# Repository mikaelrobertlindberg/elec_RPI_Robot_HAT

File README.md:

# Robot HAT D1-M1 — PCBWay prototype package

**Current fork revision: D1-M1, ten assembled prototype boards.** Use [the complete M1 PCBA archive](production/M1/Robot_HAT_M1_PCBA_10.zip), [ordering instructions](ORDERING.md) and [qualification record](QUALIFICATION.md). Original D1 production files below are historical. M1 targets a 2S battery (6.0–8.4 V) and a combined 5 V load up to 2 A; the original 5–28 V statement is superseded for this revision.

M1 corrects U12 pad/mask spacing, audio filter labels, component sourcing/pinouts and the regulator/ideal-diode circuit. It includes coherent Gerber, drills, BOM, placement, assembly drawings and dated sourcing. Native checks and export verification are recorded in the package. Physical prototype testing remains required.

## Original upstream description

> "RPI_Robot_HAT" is a raspberry pi HAT designed for small/medium size robots. It has an IMU, Dynamixel connectors and audio. Its size fits a Raspberry PI zero.

The RPI_Robot_HAT gathers:

- **IMU** over I2C + data fusion
- **Dynamixel motor communication**: both TTL and 485 to drive Dynamixel/Feetech motor (requires cable adaptation)
- **in/out audio device** with an integrated mems microphone. Wago connectors allows connection of loudspeaker and extra microphone.
- **expension Qwiic connectors**, 1 mm/3V3. Please refer to the schematic for knowing which can be use on you raspberry pi.

The RPI_Robot_HAT can be power from 5 to 28V. It is designed to use of the motor connector as an power input.

## Releases
| Release | Date       | Designer | Check  | Comments                               |
|---------|------------|----------|--------|----------------------------------------|
| A1      | 06/03/2026 | EB       | SN     | Initial drawing                        |
| B1      | 06/05/2026 | EB       | SN     |[fixed] Acc. is at 0x19 I2C address<br />[fixed] Soft reset of the audio DAC<br />[fixed] Ideal diode<br />[fixed] Know position of IMU<br />[update] Dynamixel_dir is based on Tx<br />[added] IMU can be disconnected<br />[added] IMU_IT is cabled<br />[added] Access to I2C0<br />[added] Switch off detection|
| C1      | 08/07/2026 | EB       | SN     | [fix] 3V3 on IO10/11<br />[fix] MOS direction of Ideal diode<br />[update] I2C3 is by default instead of reserved I2C|
| D1      | 06/10/2026 | EB       | Claude | [update] IMU is now LSM6DSV16XTR<br />[update] RS485 Driver<br /> [update] screwable terminals for audio|

## Basically
 - Designed with KiCAD 9.

## Rebuilding M1

The checked-in production/M1 archive is ready for supplier review. To reproduce it, use KiCad9 CLI/Python and Python3 with shapely, gerbonara and PyMuPDF, then run python build_release.py. The builder runs physical connectivity, the deliberate U12 negative control, native all-severity checks and export reconciliation before packaging. --package-only refreshes packaging from existing exports and requires an up-to-date native connectivity report; it does not export new CAD data.

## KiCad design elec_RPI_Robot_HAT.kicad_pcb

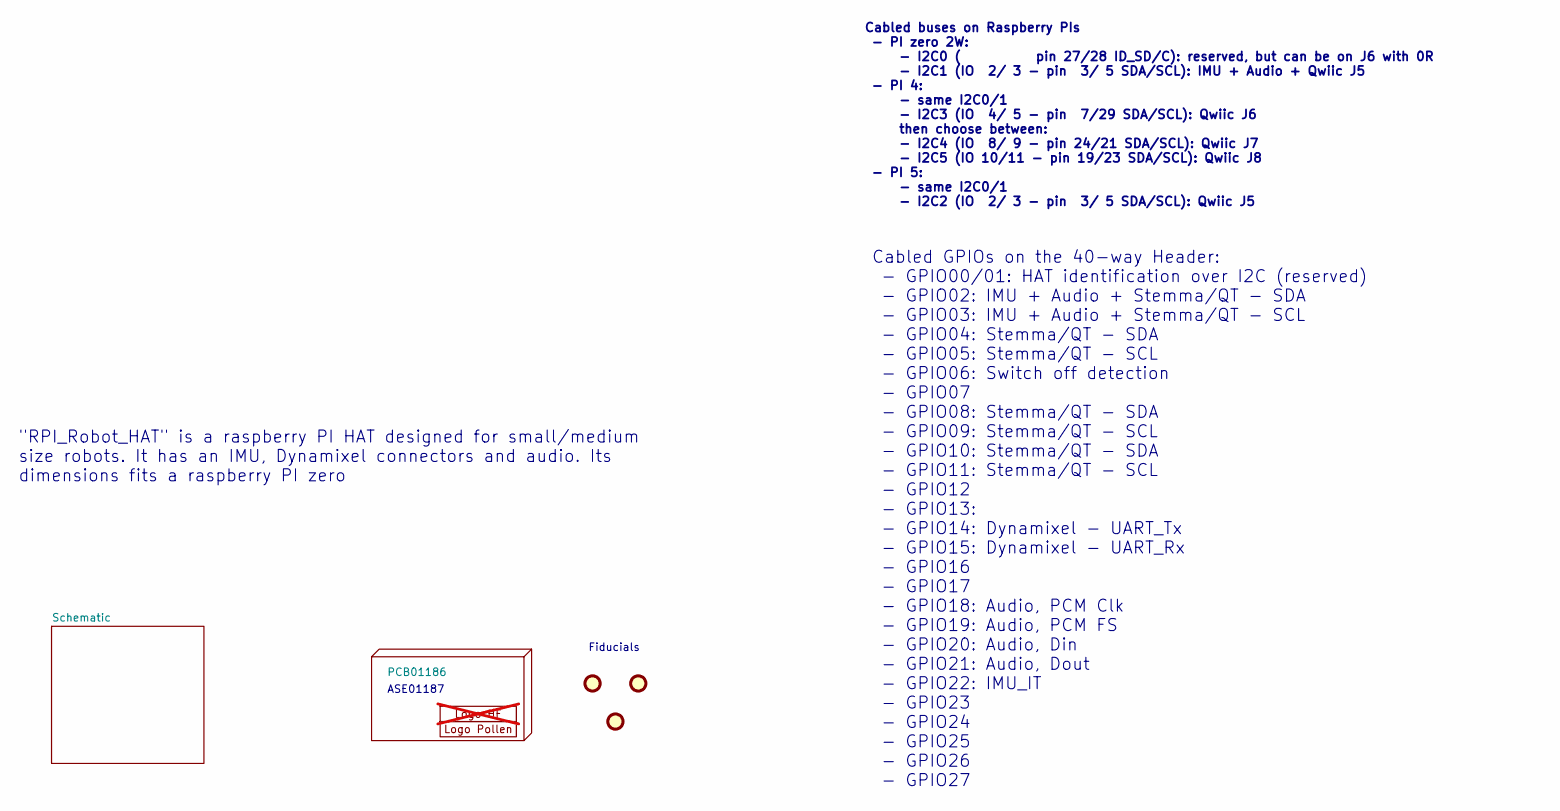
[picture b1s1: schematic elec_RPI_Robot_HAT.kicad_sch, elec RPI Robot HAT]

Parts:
FID1: DNP Fiducial; Fiducial_1mm_Mask2mm_FID1
FID2: DNP Fiducial; Fiducial_1mm_Mask2mm_FID2
FID3: DNP Fiducial; Fiducial_1mm_Mask2mm_FID3
H1: PCB01186
H2: Logo HF 2025; Logo_HF_2025_H2; not fitted
H3: DNP Logo Pollen 2021; Logo_Pollen_2021_sq_H3

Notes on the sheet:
Fiducials
Cabled buses on Raspberry PIs - PI zero 2W: - I2C0 ( pin 27/28 ID_SD/C): reserved, but can be on J6 with 0R - I2C1 (IO 2/ 3 - pin 3/ 5 SDA/SCL): IMU + Audio + Qwiic J5 - PI 4: - same I2C0/1 - I2C3 (IO 4/ 5 - pin 7/29 SDA/SCL): Qwiic J6 then choose between: - I2C4 (IO 8/ 9 - pin 24/21 SDA/SCL): Qwii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
ASE01187
"RPI_Robot_HAT" is a raspberry PI HAT designed for small/medium size robots. It has an IMU, Dynamixel connectors and audio. Its dimensions fits a raspberry PI zero
Cabled GPIOs on the 40-way Header: - GPIO00/01: HAT identification over I2C (reserved) - GPIO02: IMU + Audio + Stemma/QT - SDA - GPIO03: IMU + Audio + Stemma/QT - SCL - GPIO04: Stemma/QT - SDA - GPIO05: Stemma/QT - SCL - GPIO06: Switch off detection - GPIO07 - GPIO08: Stemma/QT - SDA - GPIO09: Stem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

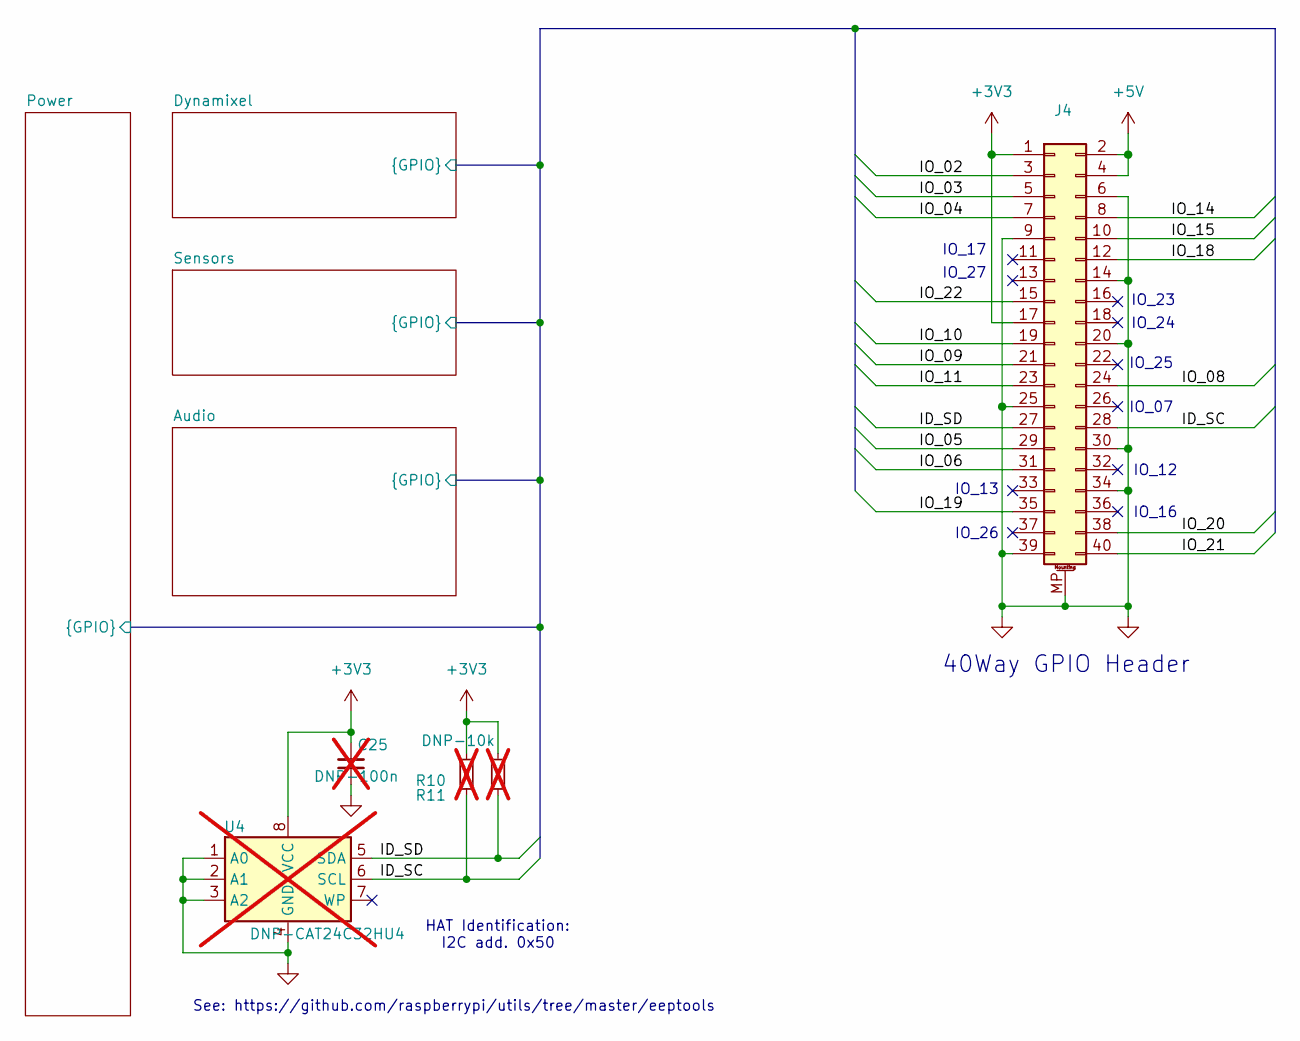
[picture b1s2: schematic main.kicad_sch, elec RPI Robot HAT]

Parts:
C25: DNP-100n; C_0402_1005Metric_C25; not fitted
J4: Female Header 2x20 SMD; PinHeader_2x20_P2.54mm_Vertical_with_rasp_HAT_zero_SMD_conn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; Part Description PinHeader_2x20_P2.54mm_Vertical; LCSC Part C2685112
R10: DNP-10k; R_0402_1005Metric_R10; not fitted
R11: DNP-10k; R_0402_1005Metric_R11; not fitted
U4: DNP-CAT24C32HU4; TDFN-8_L3.0-W2.0-P0.50-BL-EP_U4; not fitted

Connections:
+3V3: C25.2, J4.1, J4.17, R10.1, R11.1, U4.8 (VCC); also elsewhere on the board
+5V: J4.2, J4.4; also elsewhere on the board
/Schematic/Audio/ID_SC: J4.28, R10.2, U4.6 (SCL); also elsewhere on the board
/Schematic/Audio/ID_SD: J4.27, R11.2, U4.5 (SDA); also elsewhere on the board
/Schematic/Audio/IO_02: J4.3; also elsewhere on the board
/Schematic/Audio/IO_03: J4.5; also elsewhere on the board
/Schematic/Audio/IO_04: J4.7; also elsewhere on the board
/Schematic/Audio/IO_05: J4.29; also elsewhere on the board
/Schematic/Audio/IO_06: J4.31; also elsewhere on the board
/Schematic/Audio/IO_08: J4.24; also elsewhere on the board
/Schematic/Audio/IO_09: J4.21; also elsewhere on the board
/Schematic/Audio/IO_10: J4.19; also elsewhere on the board
/Schematic/Audio/IO_11: J4.23; also elsewhere on the board
/Schematic/Audio/IO_14: J4.8; also elsewhere on the board
/Schematic/Audio/IO_15: J4.10; also elsewhere on the board
/Schematic/Audio/IO_18: J4.12; also elsewhere on the board
/Schematic/Audio/IO_19: J4.35; also elsewhere on the board
/Schematic/Audio/IO_20: J4.38; also elsewhere on the board
/Schematic/Audio/IO_21: J4.40; also elsewhere on the board
/Schematic/Audio/IO_22: J4.15; also elsewhere on the board
GND: C25.1, J4.6, J4.9, J4.14, J4.20, J4.25, J4.30, J4.34, J4.39, J4.MP (MountPin), U4.1 (A0), U4.2 (A1), U4.3 (A2), U4.4 (GND); also elsewhere on the board

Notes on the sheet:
IO_07
IO_23
40Way GPIO Header
IO_13
IO_24
HAT Identification: I2C add. 0x50
IO_25
IO_17
IO_12
See: https://github.com/raspberrypi/utils/tree/master/eeptools
IO_16
IO_26
IO_27

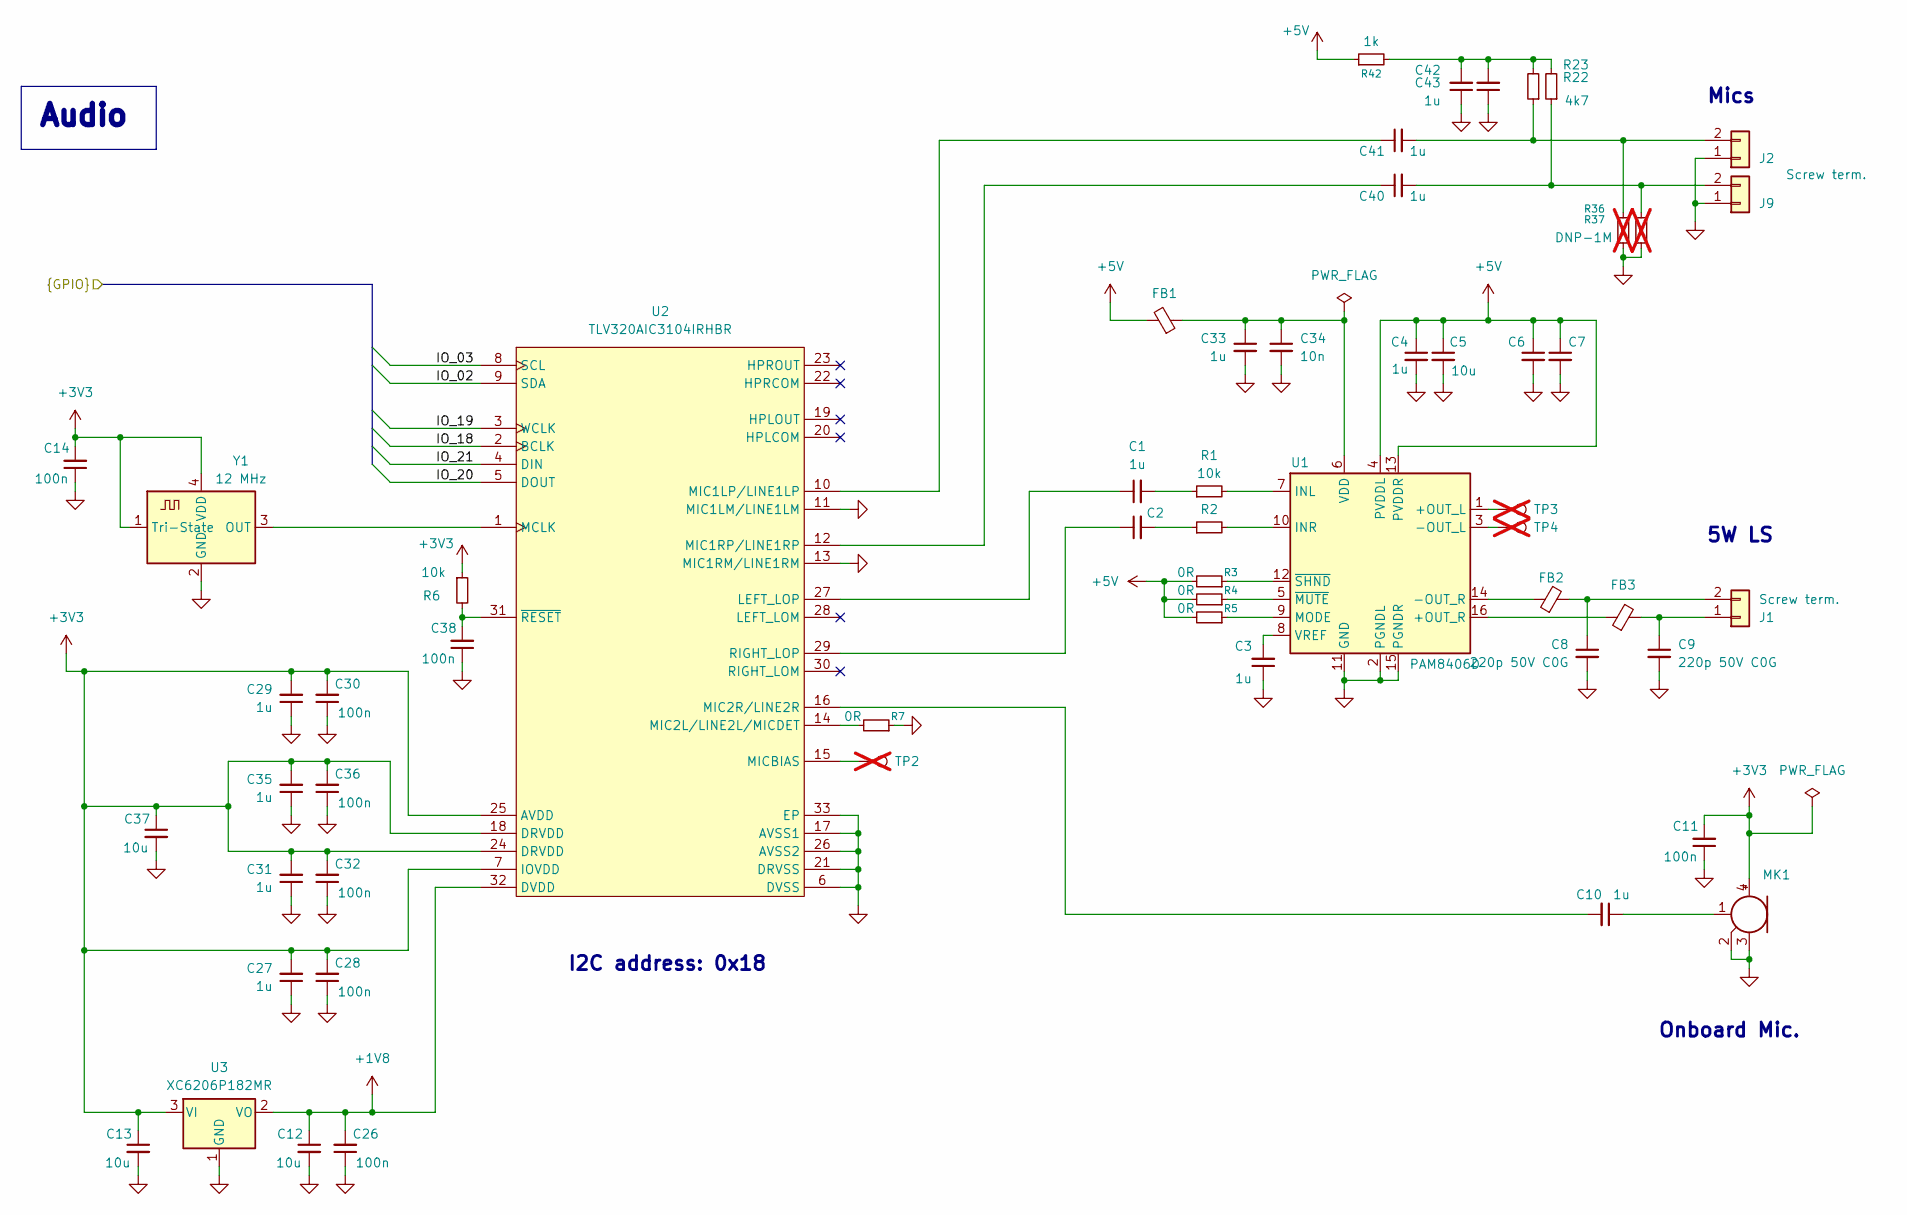
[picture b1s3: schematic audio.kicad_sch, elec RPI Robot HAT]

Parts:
C1: 1u; C_0402_1005Metric_C1; LCSC Part C52923
C2: 1u; C_0402_1005Metric_C2; LCSC Part C52923
C3: 1u; C_0402_1005Metric_C3; LCSC Part C52923
C4: 1u; C_0402_1005Metric_C4; LCSC Part C52923
C5: 10u; C_0603_1608Metric_C5; LCSC Part C1691
C6: 1u; C_0402_1005Metric_C6; LCSC Part C52923
C7: 10u; C_0603_1608Metric_C7; LCSC Part C1691
C8: 220p 50V C0G; C_0402_1005Metric_C8; LCSC Part C71693
C9: 220p 50V C0G; C_0402_1005Metric_C9; LCSC Part C71693
C10: 1u; C_0402_1005Metric_C10; LCSC Part C52923
C11: 100n; C_0402_1005Metric_C11; LCSC Part C307331
C12: 10u; C_0603_1608Metric_C12; LCSC Part C1691
C13: 10u; C_0603_1608Metric_C13; LCSC Part C1691
C14: 100n; C_0402_1005Metric_C14; LCSC Part C307331
C26: 100n; C_0402_1005Metric_C26; LCSC Part C307331
C27: 1u; C_0402_1005Metric_C27; LCSC Part C52923
C28: 100n; C_0402_1005Metric_C28; LCSC Part C307331
C29: 1u; C_0402_1005Metric_C29; LCSC Part C52923
C30: 100n; C_0402_1005Metric_C30; LCSC Part C307331
C31: 1u; C_0402_1005Metric_C31; LCSC Part C52923
C32: 100n; C_0402_1005Metric_C32; LCSC Part C307331
C33: 1u; C_0402_1005Metric_C33; LCSC Part C52923
C34: 10n; C_0402_1005Metric_C34; LCSC Part C15195
C35: 1u; C_0402_1005Metric_C35; LCSC Part C52923
C36: 100n; C_0402_1005Metric_C36; LCSC Part C307331
C37: 10u; C_0603_1608Metric_C37; LCSC Part C1691
C38: 100n; C_0402_1005Metric_C38; LCSC Part C307331
C40: 1u; C_0402_1005Metric_C40; LCSC Part C52923
C41: 1u; C_0402_1005Metric_C41; LCSC Part C52923
C42: 1u; C_0402_1005Metric_C42; LCSC Part C52923
C43: 1u; C_0402_1005Metric_C43; LCSC Part C52923
FB1: 0.3A 600R@100MHz; L_0402_1005Metric_FB1; LCSC Part C76884
FB2: 2A - 120R@100MHz; L_0402_1005Metric_FB2; LCSC Part C88970
FB3: 2A - 120R@100MHz; L_0402_1005Metric_FB3; LCSC Part C88970
J1: Screw term.; CONN-TH_DB125-2.54-2P-GN_J1; LCSC Part C918120
J2: Screw term.; CONN-TH_DB125-2.54-2P-GN_J2; LCSC Part C918120
J9: Screw term.; CONN-TH_DB125-2.54-2P-GN_J9; LCSC Part C918120
MK1: Microphone_MEMS; MIC-SMD_4P-L2.8-W1.9-P1.84-TL_MK1; LCSC Part C7587901
R1: 10k; R_0402_1005Metric_R1; LCSC Part C25744
R2: 10k; R_0402_1005Metric_R2; LCSC Part C25744
R3: 0R; R_0402_1005Metric_R3; LCSC Part C17168
R4: 0R; R_0402_1005Metric_R4; LCSC Part C17168
R5: 0R; R_0402_1005Metric_R5; LCSC Part C17168
R6: 10k; R_0402_1005Metric_R6; LCSC Part C25744
R7: 0R; R_0402_1005Metric_R7; LCSC Part C17168
R22: 4k7; R_0402_1005Metric_R22; LCSC Part C105871
R23: 4k7; R_0402_1005Metric_R23; LCSC Part C105871
R36: DNP-1M; R_0402_1005Metric_R36; not fitted
R37: DNP-1M; R_0402_1005Metric_R37; not fitted
R42: 1k; R_0402_1005Metric_R42; LCSC Part C105637
TP2: TestPoint; TestPoint_Loop_D2.50mm_Drill1.0mm_LowProfile_TP2; not fitted
TP3: TestPoint; TestPoint_Loop_D2.50mm_Drill1.0mm_LowProfile_TP3; not fitted
TP4: TestPoint; TestPoint_Loop_D2.50mm_Drill1.0mm_LowProfile_TP4; not fitted
U1: PAM8406D; SOIC-16_3.9x9.9mm_P1.27mm_U1; LCSC Part C86270
U2: TLV320AIC3104IRHBR; VQFN-32-1EP_5x5mm_P0.5mm_EP3.5x3.5mm_U2; LCSC Part C181753
U3: XC6206P182MR; SOT-23-3_U3; LCSC Part C347373
Y1: 12 MHz; Oscillator_SMD_Abracon_ASDMB-4Pin_2.5x2.0mm_Y1; LCSC Part C7425459

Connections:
+1V8: C12.1, C26.2, U2.32 (DVDD), U3.2 (VO)
+3V3: C11.2, C13.1, C14.2, C27.2, C28.2, C29.2, C30.2, C31.2, C32.2, C35.2, C36.2, C37.1, MK1.4 (+), R6.1, U2.7 (IOVDD), U2.18 (DRVDD), U2.24 (DRVDD), U2.25 (AVDD), U3.3 (VI), Y1.1 (Tri-State), Y1.4 (VDD); also elsewhere on the board
+5V: C4.1, C5.1, C6.1, C7.1, FB1.2, R3.2, R4.2, R5.2, R42.1, U1.4 (PVDDL), U1.13 (PVDDR); also elsewhere on the board
/Schematic/Audio/IO_02: U2.9 (SDA); also elsewhere on the board
/Schematic/Audio/IO_03: U2.8 (SCL); also elsewhere on the board
/Schematic/Audio/IO_18: U2.2 (BCLK); also elsewhere on the board
/Schematic/Audio/IO_19: U2.3 (WCLK); also elsewhere on the board
/Schematic/Audio/IO_20: U2.5 (DOUT); also elsewhere on the board
/Schematic/Audio/IO_21: U2.4 (DIN); also elsewhere on the board
GND: C3.1, C4.2, C5.2, C6.2, C7.2, C8.2, C9.2, C11.1, C12.2, C13.2, C14.1, C26.1, C27.1, C28.1, C29.1, C30.1, C31.1, C32.1, C33.2, C34.2, C35.1, C36.1, C37.2, C38.1, C42.1, C43.1, J2.1, J9.1, MK1.2 (-), MK1.3 (-), R7.1, R36.1, R37.1, U1.2 (PGNDL), U1.11 (GND), U1.15 (PGNDR), U2.6 (DVSS), U2.11 (MIC1LM/LINE1LM), U2.13 (MIC1RM/LINE1RM), U2.17 (AVSS1), U2.21 (DRVSS), U2.26 (AVSS2), U2.33 (EP), U3.1 (GND), Y1.2 (GND); also elsewhere on the board
unnamed: C1.2, R1.1
unnamed: C2.2, R2.1
unnamed: C10.1, MK1.1 (-)
unnamed: C42.2, C43.2, R22.2, R23.2, R42.2
unnamed: C9.1, FB3.2, J1.1
unnamed: C8.1, FB2.2, J1.2
unnamed: C41.2, J2.2, R22.1, R36.2
unnamed: C40.2, J9.2, R23.1, R37.2
unnamed: TP3.1, U1.1 (+OUT_L)
unnamed: FB3.1, U1.16 (+OUT_R)
unnamed: TP4.1, U1.3 (-OUT_L)
unnamed: FB2.1, U1.14 (-OUT_R)
unnamed: R1.2, U1.7 (INL)
unnamed: R2.2, U1.10 (INR)
unnamed: R5.1, U1.9 (MODE)
unnamed: C33.1, C34.1, FB1.1, U1.6 (VDD)
unnamed: C3.2, U1.8 (VREF)
unnamed: R4.1, U1.5 (~MUTE)
unnamed: R3.1, U1.12 (~SHND)
unnamed: C1.1, U2.27 (LEFT_LOP)
unnamed: U2.1 (MCLK), Y1.3 (OUT)
unnamed: C41.1, U2.10 (MIC1LP/LINE1LP)
unnamed: C40.1, U2.12 (MIC1RP/LINE1RP)
unnamed: R7.2, U2.14 (MIC2L/LINE2L/MICDET)
unnamed: C10.2, U2.16 (MIC2R/LINE2R)
unnamed: TP2.1, U2.15 (MICBIAS)
unnamed: C2.1, U2.29 (RIGHT_LOP)
unnamed: C38.2, R6.2, U2.31 (~RESET)

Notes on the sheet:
Onboard Mic.
5W LS
Mics
I2C address: 0x18
Audio

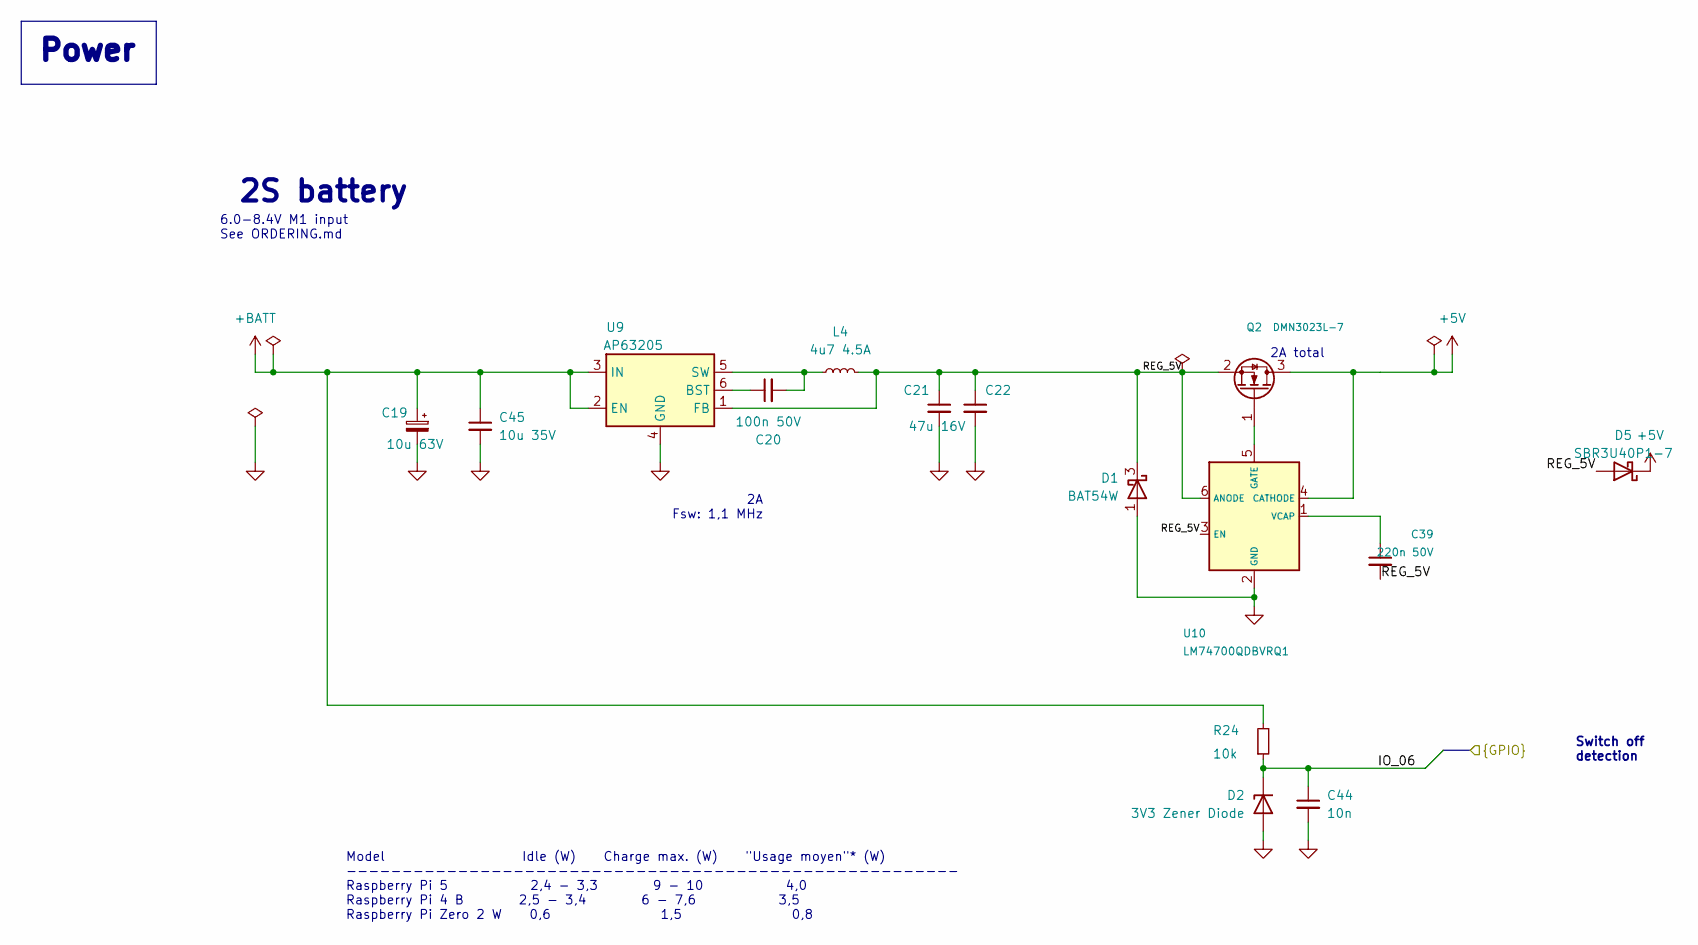
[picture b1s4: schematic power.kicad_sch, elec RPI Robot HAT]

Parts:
C19: 10u 63V; Panasonic_FK_D_6.3x5.8_C19
C20: 100n 50V; C_0402_1005Metric_C20; LCSC Part C307331
C21: 47u 16V; C_1206_C21; LCSC Part C385047
C22: 47u 16V; C_1206_C22; LCSC Part C385047
C39: 220n 50V; C_0805_C39; LCSC Part C86042
C44: 10n; C_0402_1005Metric_C44; LCSC Part C15195
C45: 10u 35V; C_0805_2012Metric_C45; LCSC Part C33546007
D1: BAT54W; SOT-323_SC-70_D1
D2: 3V3 Zener Diode; D_SOD-123_D2; LCSC Part C19077392
D5: SBR3U40P1-7; D_PowerDI123_D5; LCSC Part C97127
L4: 4u7 4.5A; Eaton_SDCHA1V6045_L4
Q2: DMN3023L-7; TSOT-23_Q2; LCSC Part C443825
R24: 10k; R_0402_1005Metric_R24; LCSC Part C25744
U9: AP63205; TSOT-23-6_U9; LCSC Part C2071056
U10: LM74700QDBVRQ1; LM74700_DBV_U10; LCSC Part C2941042

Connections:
+5V: D5.1 (K), Q2.3 (D), U10.4 (CATHODE); also elsewhere on the board
+BATT: C19.1, C45.1, R24.2, U9.2 (EN), U9.3 (IN); also elsewhere on the board
/Schematic/Audio/IO_06: C44.1, D2.1 (K), R24.1; also elsewhere on the board
/Schematic/Power/REG_5V: C21.1, C22.1, C39.2, D1.3 (K), D5.2 (A), L4.1, Q2.2 (S), U9.1 (FB), U10.3 (EN), U10.6 (ANODE)
GND: C19.2, C21.2, C22.2, C44.2, C45.2, D1.1 (A), D2.2 (A), U9.4 (GND), U10.2 (GND); also elsewhere on the board
unnamed: Q2.1 (G), U10.5 (GATE)
unnamed: C20.1, U9.6 (BST)
unnamed: C20.2, L4.2, U9.5 (SW)
unnamed: C39.1, U10.1 (VCAP)

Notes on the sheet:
Switch off detection
2A total
2S battery
Model Idle (W) Charge max. (W) "Usage moyen"* (W) ------------------------------------------------------- Raspberry Pi 5 2,4 - 3,3 9 - 10 4,0 Raspberry Pi 4 B 2,5 - 3,4 6 - 7,6 3,5 Raspberry Pi Zero 2 W 0,6 1,5 0,8
6.0-8.4V M1 input See ORDERING.md
2A Fsw: 1,1 MHz
Power

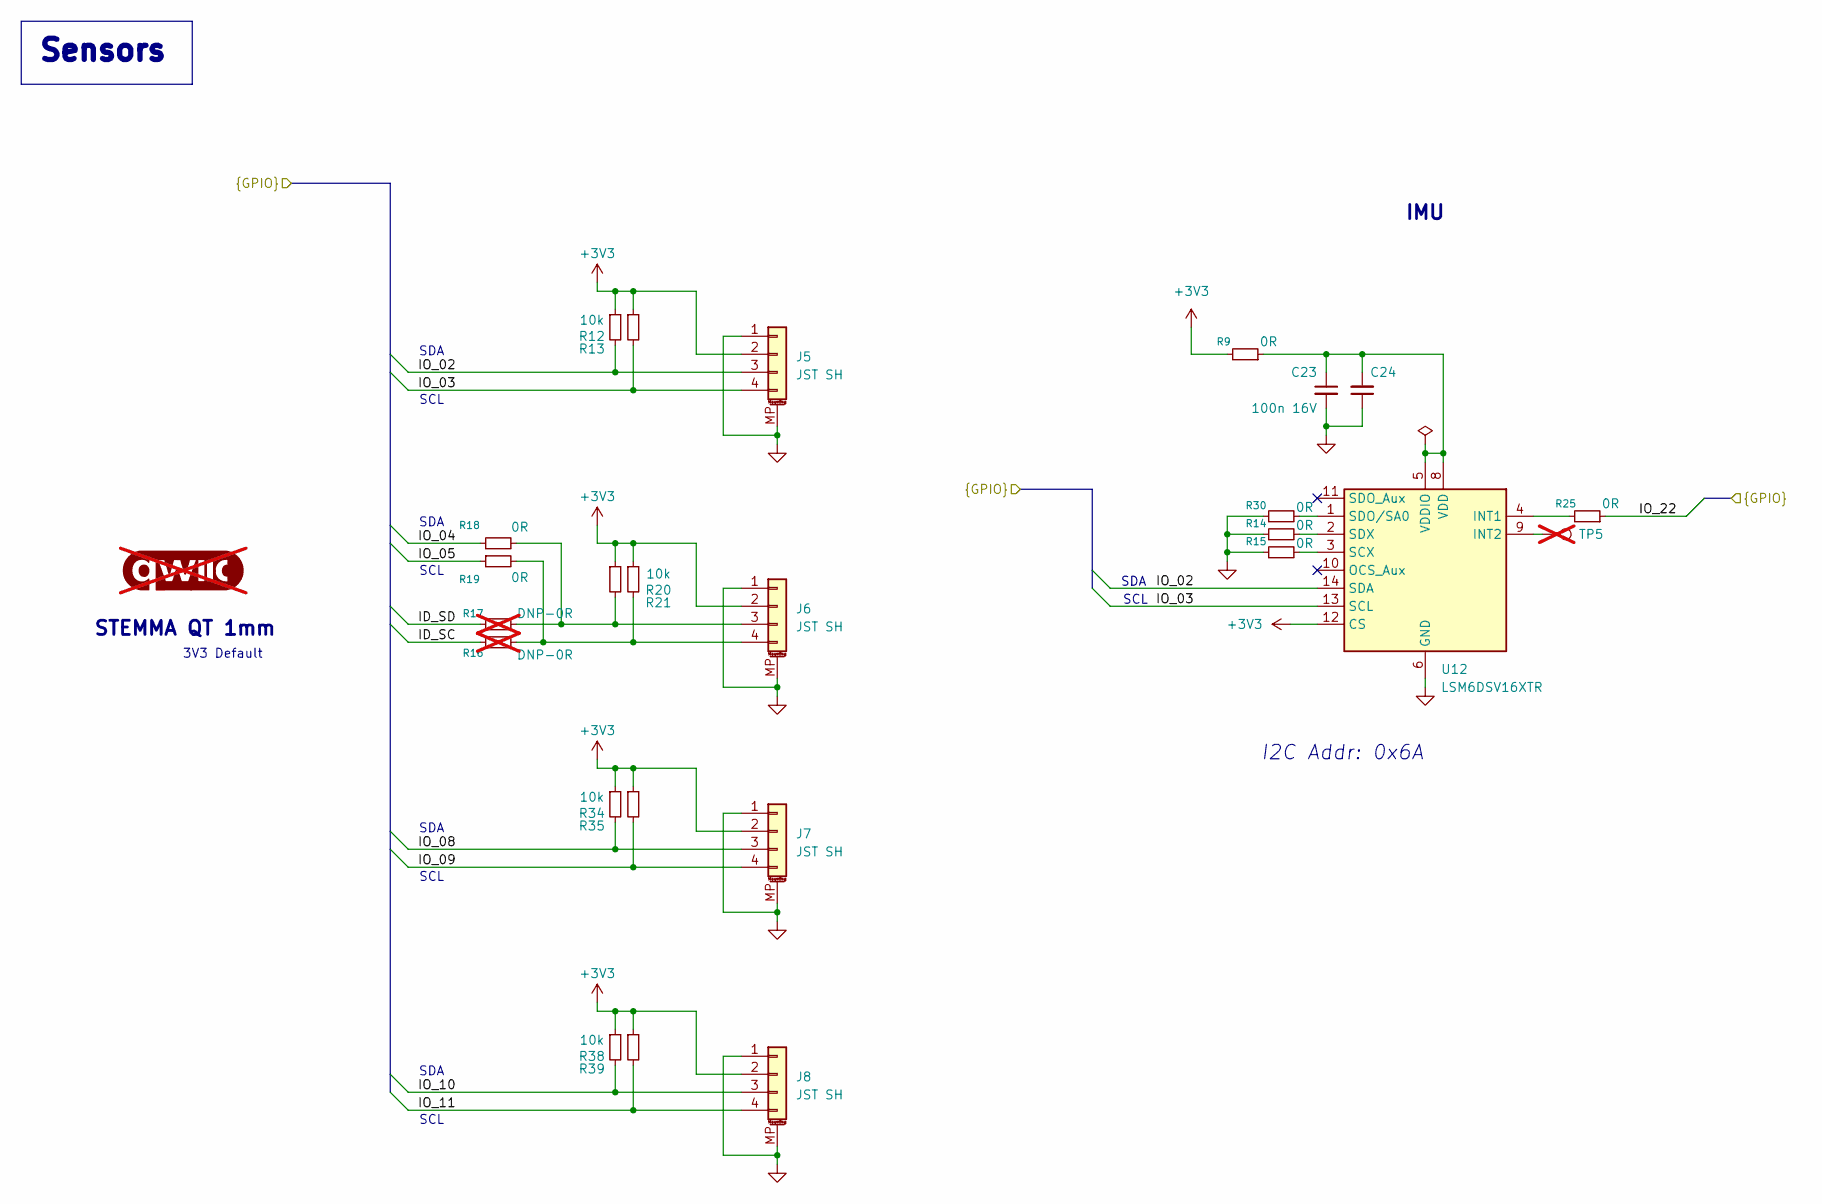
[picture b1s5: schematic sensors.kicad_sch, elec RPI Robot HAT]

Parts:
C23: 100n 16V; C_0402_1005Metric_C23; LCSC Part C1525
C24: 100n 16V; C_0402_1005Metric_C24; LCSC Part C1525
G1: qwiic_Logo; Logo_qwiic_5mm_G1; not fitted
J5: JST SH; JST_SH_BM04B-SRSS-TB_1x04-1MP_P1.00mm_Vertical_J5; LCSC Part C160390
J6: JST SH; JST_SH_BM04B-SRSS-TB_1x04-1MP_P1.00mm_Vertical_J6; LCSC Part C160390
J7: JST SH; JST_SH_BM04B-SRSS-TB_1x04-1MP_P1.00mm_Vertical_J7; LCSC Part C160390
J8: JST SH; JST_SH_BM04B-SRSS-TB_1x04-1MP_P1.00mm_Vertical_J8; LCSC Part C160390
R9: 0R; R_0402_1005Metric_R9; LCSC Part C17168
R12: 10k; R_0402_1005Metric_R12; LCSC Part C25744
R13: 10k; R_0402_1005Metric_R13; LCSC Part C25744
R14: 0R; R_0402_1005Metric_R14; LCSC Part C17168
R15: 0R; R_0402_1005Metric_R15; LCSC Part C17168
R16: DNP-0R; R_0402_1005Metric_R16; not fitted
R17: DNP-0R; R_0402_1005Metric_R17; not fitted
R18: 0R; R_0402_1005Metric_R18; LCSC Part C17168
R19: 0R; R_0402_1005Metric_R19; LCSC Part C17168
R20: 10k; R_0402_1005Metric_R20; LCSC Part C25744
R21: 10k; R_0402_1005Metric_R21; LCSC Part C25744
R25: 0R; R_0402_1005Metric_R25; LCSC Part C17168
R30: 0R; R_0402_1005Metric_R30; LCSC Part C17168
R34: 10k; R_0402_1005Metric_R34; LCSC Part C25744
R35: 10k; R_0402_1005Metric_R35; LCSC Part C25744
R38: 10k; R_0402_1005Metric_R38; LCSC Part C25744
R39: 10k; R_0402_1005Metric_R39; LCSC Part C25744
TP5: TestPoint; TestPoint_Pad_D1.0mm_TP5; not fitted
U12: LSM6DSV16XTR; LSM6DSV16X_PCBWay_020_U12; LCSC Part C5267406

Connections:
+3V3: J5.2, J6.2, J7.2, J8.2, R9.2, R12.1, R13.1, R20.1, R21.1, R34.1, R35.1, R38.1, R39.1, U12.12 (CS); also elsewhere on the board
/Schematic/Audio/ID_SC: R16.1; also elsewhere on the board
/Schematic/Audio/ID_SD: R17.1; also elsewhere on the board
/Schematic/Audio/IO_02: J5.3, R12.2, U12.14 (SDA); also elsewhere on the board
/Schematic/Audio/IO_03: J5.4, R13.2, U12.13 (SCL); also elsewhere on the board
/Schematic/Audio/IO_04: R18.1; also elsewhere on the board
/Schematic/Audio/IO_05: R19.1; also elsewhere on the board
/Schematic/Audio/IO_08: J7.3, R34.2; also elsewhere on the board
/Schematic/Audio/IO_09: J7.4, R35.2; also elsewhere on the board
/Schematic/Audio/IO_10: J8.3, R38.2; also elsewhere on the board
/Schematic/Audio/IO_11: J8.4, R39.2; also elsewhere on the board
/Schematic/Audio/IO_22: R25.1; also elsewhere on the board
GND: C23.2, C24.1, J5.1, J5.MP (MountPin), J6.1, J6.MP (MountPin), J7.1, J7.MP (MountPin), J8.1, J8.MP (MountPin), R14.1, R15.1, R30.1, U12.6 (GND), U12.7 (GND); also elsewhere on the board
unnamed: J6.3, R17.2, R18.2, R20.2
unnamed: J6.4, R16.2, R19.2, R21.2
unnamed: R25.2, U12.4 (INT1)
unnamed: TP5.1, U12.9 (INT2)
unnamed: R15.2, U12.3 (SCX)
unnamed: R30.2, U12.1 (SDO/SA0)
unnamed: R14.2, U12.2 (SDX)
unnamed: C23.1, C24.2, R9.1, U12.5 (VDDIO), U12.8 (VDD)

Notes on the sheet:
SCL
SDA
STEMMA QT 1mm
3V3 Default
IMU
I2C Addr: 0x6A
Sensors

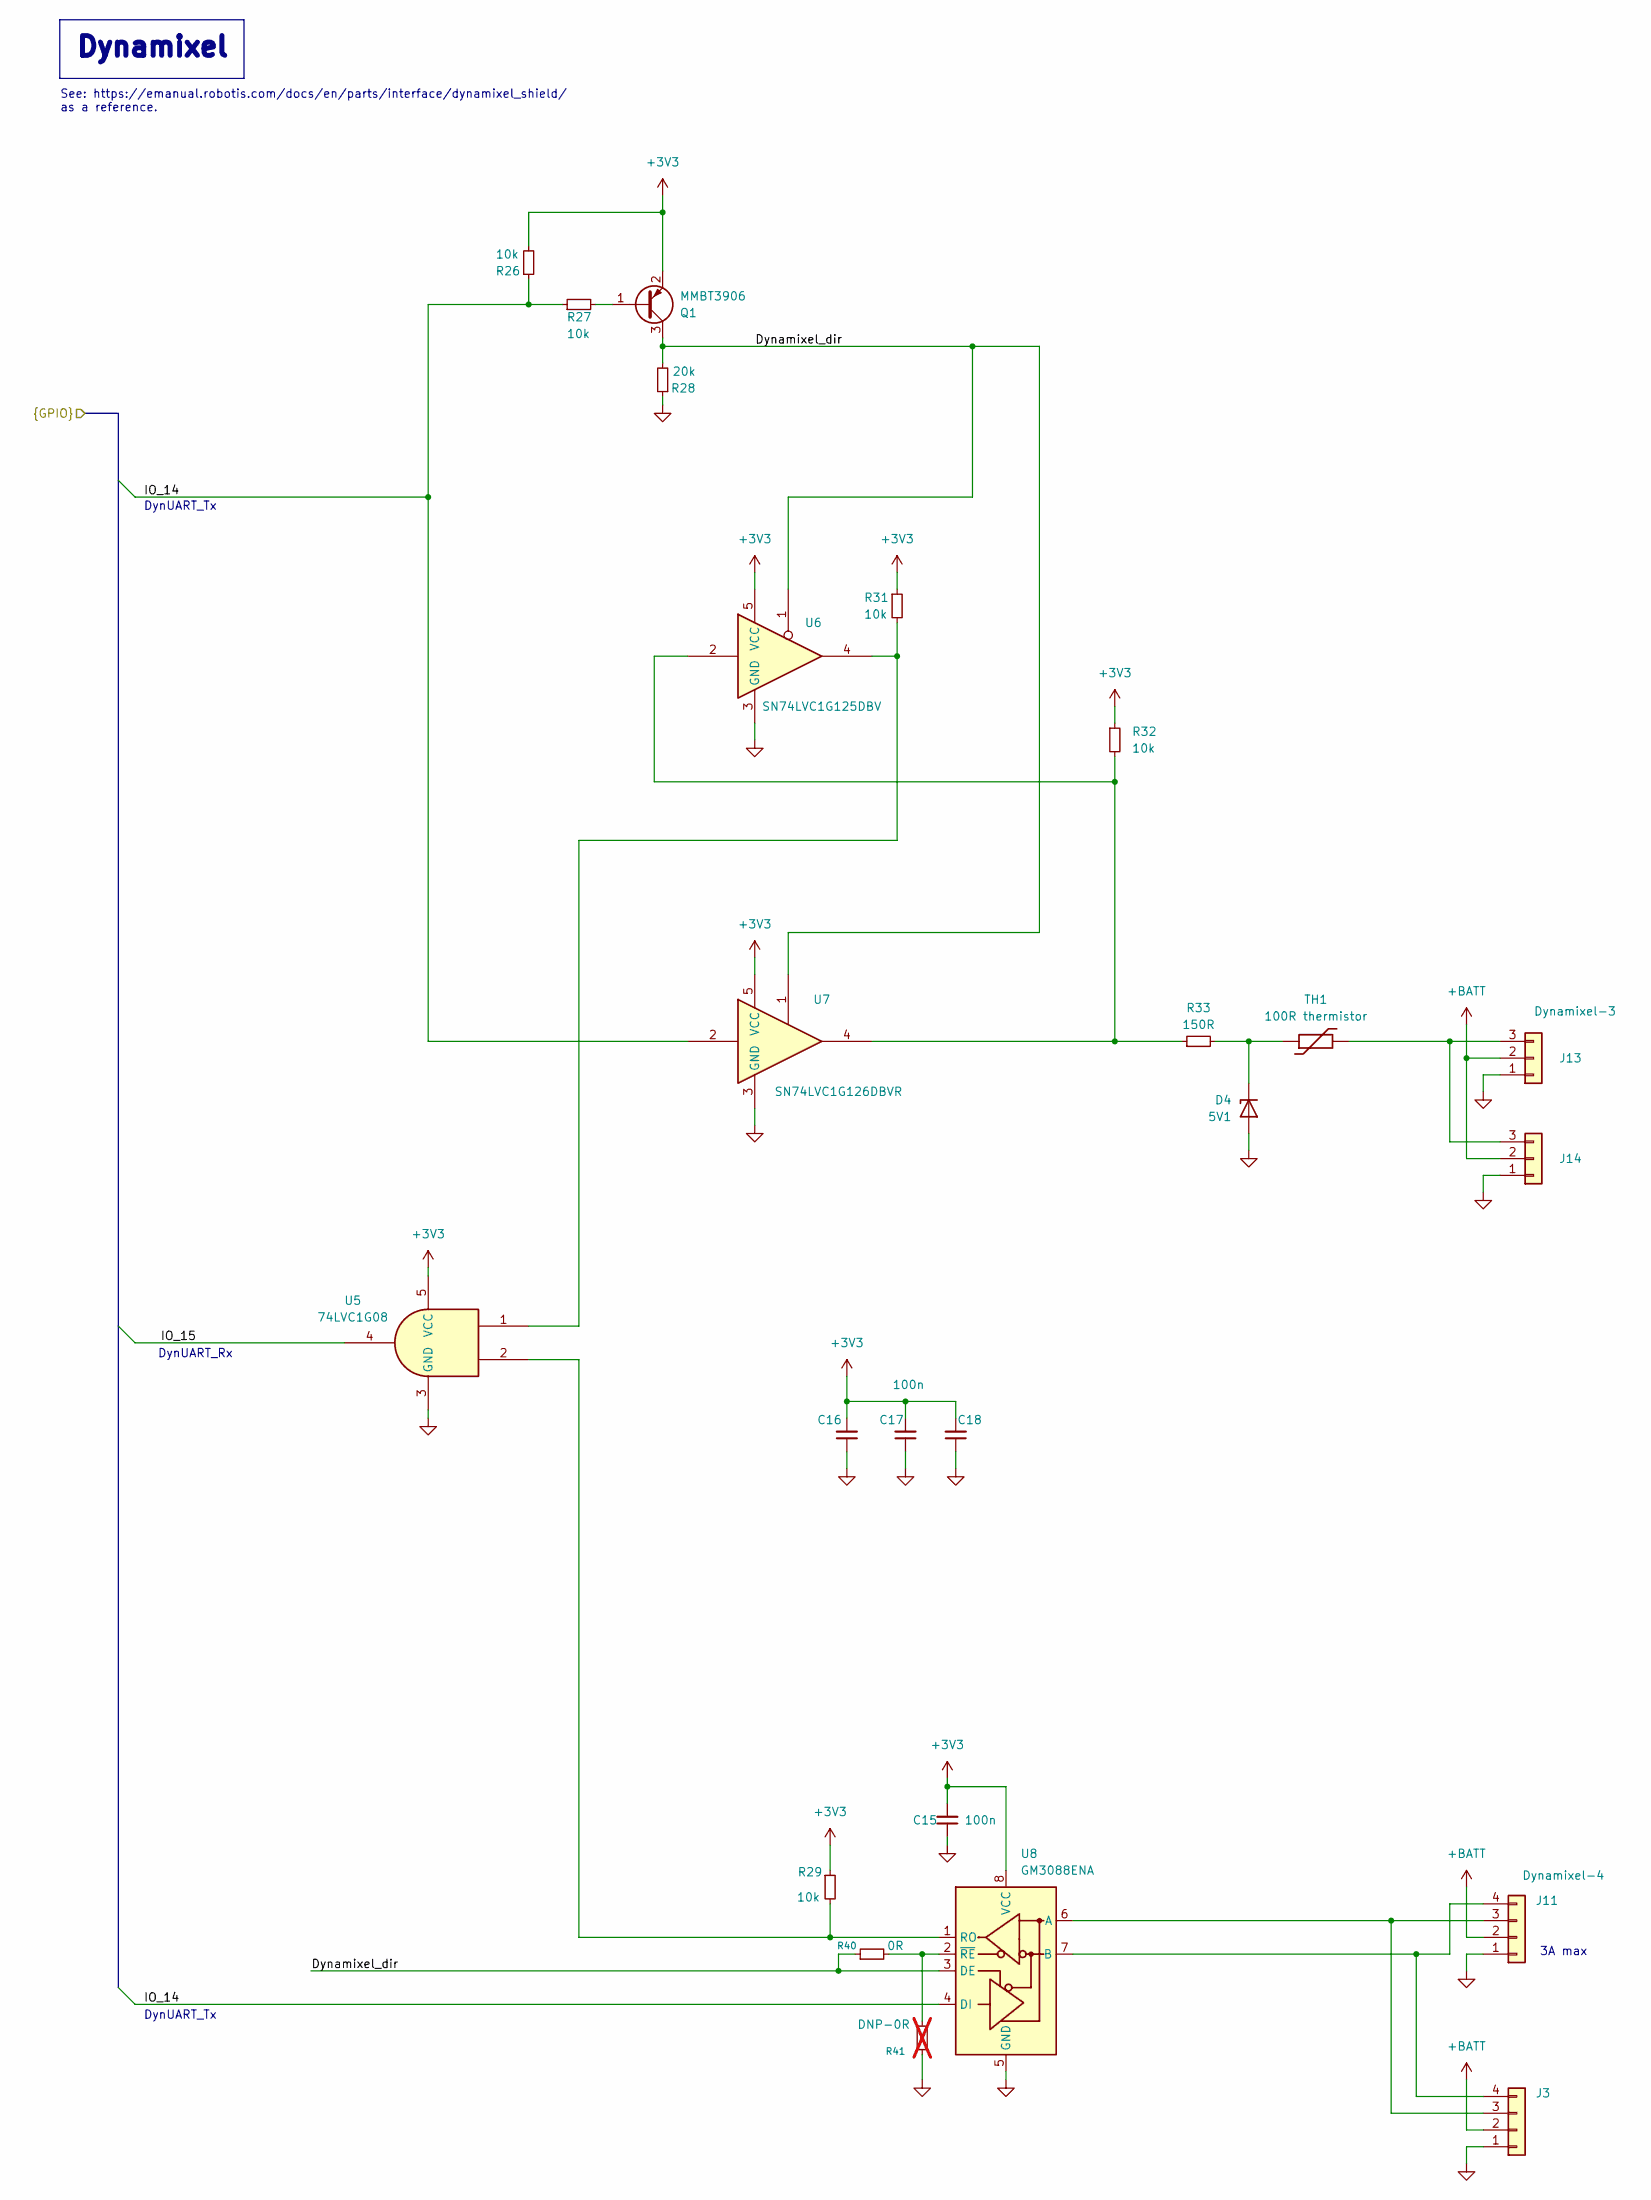
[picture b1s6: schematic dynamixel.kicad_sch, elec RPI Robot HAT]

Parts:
C15: 100n; C_0402_1005Metric_C15; LCSC Part C307331
C16: 100n; C_0402_1005Metric_C16; LCSC Part C307331
C17: 100n; C_0402_1005Metric_C17; LCSC Part C307331
C18: 100n; C_0402_1005Metric_C18; LCSC Part C307331
D4: 5V1; D_SOD-323_D4; LCSC Part C151348
J3: Dynamixel-4; JST_EH_B4B-EH-A_1x04_P2.50mm_Vertical_J3; LCSC Part C160258
J11: Dynamixel-4; JST_EH_B4B-EH-A_1x04_P2.50mm_Vertical_J11; LCSC Part C160258
J13: Dynamixel-3; JST_EH_B3B-EH-A_1x03_P2.50mm_Vertical_J13; LCSC Part C160259
J14: Dynamixel-3; JST_EH_B3B-EH-A_1x03_P2.50mm_Vertical_J14; LCSC Part C160259
Q1: MMBT3906; SOT-23_Q1; LCSC Part C727128
R26: 10k; R_0402_1005Metric_R26; LCSC Part C25744
R27: 10k; R_0402_1005Metric_R27; LCSC Part C25744
R28: 20k; R_0402_1005Metric_R28; LCSC Part C25765
R29: 10k; R_0402_1005Metric_R29; LCSC Part C25744
R31: 10k; R_0402_1005Metric_R31; LCSC Part C25744
R32: 10k; R_0402_1005Metric_R32; LCSC Part C25744
R33: 150R; R_0402_1005Metric_R33; LCSC Part C2909321
R40: 0R; R_0402_1005Metric_R40; LCSC Part C17168
R41: DNP-0R; R_0402_1005Metric_R41; not fitted
TH1: 100R thermistor; R_0603_1608Metric_TH1; LCSC Part C913703
U5: 74LVC1G08; SOT-23-5_U5; LCSC Part C7666
U6: SN74LVC1G125DBV; SOT-23-5_U6; LCSC Part C23654
U7: SN74LVC1G126DBVR; SOT-23-5_U7; LCSC Part C7834
U8: GM3088ENA; DFN-8-1EP_3x3mm_P0.65mm_EP1.2x2.15mm_U8; LCSC Part C49423279

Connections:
+3V3: C15.2, C16.2, C17.2, C18.2, Q1.2 (E), R26.2, R29.1, R31.1, R32.1, U5.5 (VCC), U6.5 (VCC), U7.5 (VCC), U8.8 (VCC); also elsewhere on the board
+BATT: J3.2, J11.2, J13.2, J14.2; also elsewhere on the board
/Schematic/Audio/IO_14: R26.1, R27.1, U7.2, U8.4 (DI); also elsewhere on the board
/Schematic/Audio/IO_15: U5.4; also elsewhere on the board
/Schematic/Dynamixel/Dynamixel_dir: Q1.3 (C), R28.2, R40.1, U6.1, U7.1, U8.3 (DE)
GND: C15.1, C16.1, C17.1, C18.1, D4.2 (A), J3.1, J11.1, J13.1, J14.1, R28.1, R41.1, U5.3 (GND), U6.3 (GND), U7.3 (GND), U8.5 (GND); also elsewhere on the board
unnamed: D4.1 (K), R33.2, TH1.1
unnamed: J3.3, J11.3, U8.6 (A)
unnamed: J3.4, J11.4, U8.7 (B)
unnamed: J13.3, J14.3, TH1.2
unnamed: Q1.1 (B), R27.2
unnamed: R31.2, U5.1, U6.4
unnamed: R32.2, R33.1, U6.2, U7.4
unnamed: R29.2, U5.2, U8.1 (RO)
unnamed: R40.2, R41.2, U8.2 (~RE)

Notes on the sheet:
DynUART_Tx
DynUART_Rx
See: https://emanual.robotis.com/docs/en/parts/interface/dynamixel_shield/ as a reference.
3A max
Dynamixel
